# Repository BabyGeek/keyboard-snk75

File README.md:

# keyboard SnK<sup>75</sup>

V1 prototype in progress

----

The name "SnK<sup>75</sup>" come from my online name MrSnkiiKyz and 75 because it is a 75% layout

### Pictures will go there when V1 prototype will be done

## Features scheduled
* The PCB
    * handle up to 84 MX Swicthes
    * USB-C connected
    * RGB backligt for each swicth (South facing)
    * RGB Underglow
    * programmable with QMK
* The Layout is ISO only (Layout legends based on MacOS ISO-FR layout)
* 7° Typing angle case

## Features done
* The keyboard layout YES - you can [check it there](http://www.keyboard-layout-editor.com/##@@_a:7%3B&=Esc&=%0A%0A%0A%0AF1&=%0A%0A%0A%0AF2&=%0A%0A%0A%0AF3&=%0A%0A%0A%0AF4&=%0A%0A%0A%0AF5&=%0A%0A%0A%0AF6&=%0A%0A%0A%0AF7&=%0A%0A%0A%0AF8&=%0A%0A%0A%0AF9&=%0A%0A%0A%0AF10&=%0A%0A%0A%0AF11&=%0A%0A%0A%0AF12&=&=&=%3B&@_a:0%3B&=%23%0A%0A%0A%2F@%0A~%0A%60&=%0A%0A%0A%2F&%0A!%0A1&=%0A%0A%0Aé%0A%2F@%0A2&=%0A%0A%0A%22%0A%23%0A3&=%0A%0A%0A'%0A$%0A4&=%0A%0A%0A(%0A%25%0A5&=%0A%0A%0A§%0A%5E%0A6&=%0A%0A%0Aè%0A%2F&%0A7&=%0A%0A%0A!%0A*%0A8&=%0A%0A%0Aç%0A(%0A9&=%0A%0A%0Aà%0A)%0A0&=%25%0A%0A%0A)%0A%2F_%0A-&=%2F_%0A%0A%0A-%0A+%0A%2F=&_a:7&w:2%3B&=%0A%0A%0A%0ABackspace&=%0A%0A%0A%0AHome%3B&@_w:1.5%3B&=%0A%0A%0A%0ATab&_a:4%3B&=A%0A%0A%0A%0AQ&=Z%0A%0A%0A%0AW&=E%0A%0A%0A%0AE&=R%0A%0A%0A%0AR&=T%0A%0A%0A%0AT&=Y%0A%0A%0A%0AY&=U%0A%0A%0A%0AU&=I%0A%0A%0A%0AI&=O%0A%0A%0A%0AO&=P%0A%0A%0A%0AP&_a:0%3B&=¨%0A%0A%0A%5E%0A%7B%0A%5B&=*%0A%0A%0A€%0A%7D%0A%5D%0A%0A%0A%0A%0A$&_x:0.25&a:7&w:1.25&h:2&w2:1.5&h2:1&x2:-0.25%3B&=%0A%0A%0A%0AEnter&=%0A%0A%0A%0APage%20Up%3B&@_w:1.75%3B&=%0A%0A%0A%0ACaps%20Lock&_a:4%3B&=Q%0A%0A%0A%0AA&=S%0A%0A%0A%0AS&=D%0A%0A%0A%0AD&=F%0A%0A%0A%0AF&=G%0A%0A%0A%0AG&=H%0A%0A%0A%0AH&=J%0A%0A%0A%0AJ&=K%0A%0A%0A%0AK&=L%0A%0A%0A%0AL&_a:0%3B&=M%0A%0A%0A%0A%2F:%0A%2F%3B&=N%0A%0A%0A%0A%22%0A'&_a:4%3B&=£%0A%0A%0A%60&_x:1.25&a:7%3B&=%0A%0A%0A%0APage%20Down%3B&@_w:1.25%3B&=%0A%0A%0A%0AShift&_a:4%3B&=%3C%0A%0A%0A%3E&=W%0A%0A%0A%0AZ&=X%0A%0A%0A%0AX&=C%0A%0A%0A%0AC&=V%0A%0A%0A%0AV&=B%0A%0A%0A%0AB&=N%0A%0A%0A%0AN&=%3F%0A%0A%0A,%0AM&=.%0A,%0A%0A%2F%3B%0A%3C&=%2F%2F%0A.%0A%0A%2F:%0A%3E&_a:0%3B&=+%0A%0A%0A%2F=%0A%2F%2F%0A%3F&_a:7&w:1.75%3B&=%0A%0A%0A%0AShift&=%0A%0A%0A%0A↑&=%0A%0A%0A%0AEnd%3B&@_w:1.25%3B&=%0A%0A%0A%0ACtrl&_w:1.25%3B&=%0A%0A%0A%0AWin&_w:1.25%3B&=%0A%0A%0A%0AAlt&_w:6.25%3B&=&=%0A%0A%0A%0AAlt&=%0A%0A%0A%0AFn&=%0A%0A%0A%0ACtrl&=%0A%0A%0A%0A←&=%0A%0A%0A%0A↓&=%0A%0A%0A%0A→)

* The PCB schematics - YES it is supposed to be good
* The PCB Keys layout - YES
* The PCB Routes - In progress

### THEN 

* The PCB Prototype - Not yet
* Connectivity PCB Test - Not yet

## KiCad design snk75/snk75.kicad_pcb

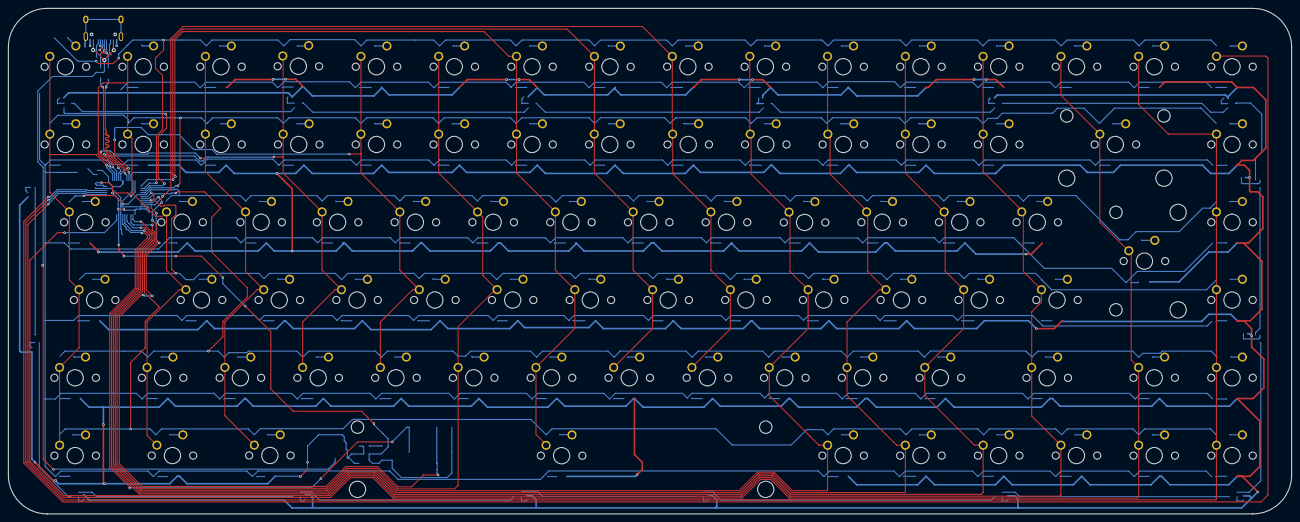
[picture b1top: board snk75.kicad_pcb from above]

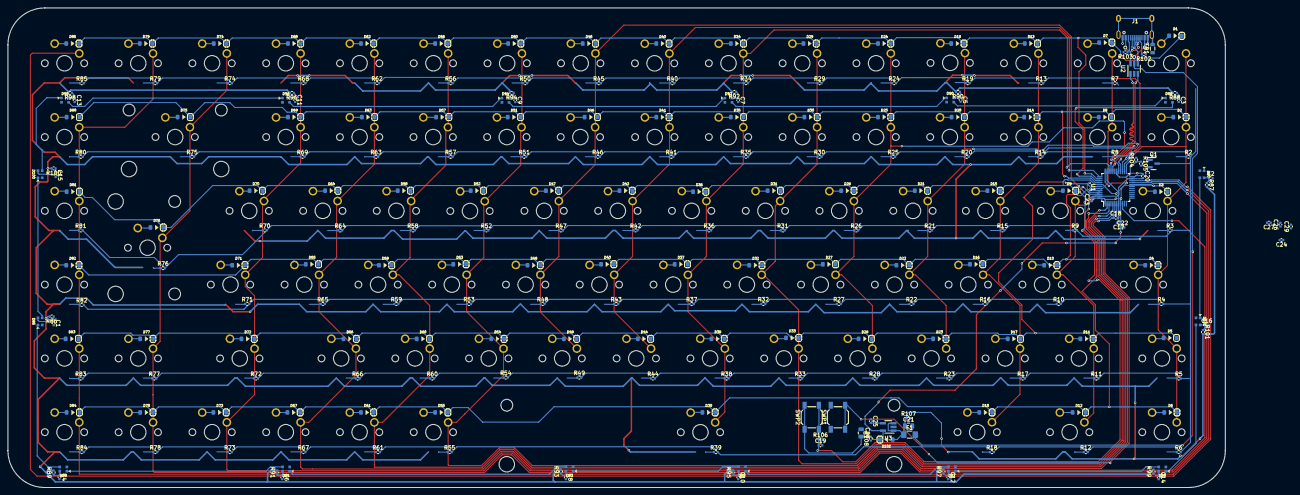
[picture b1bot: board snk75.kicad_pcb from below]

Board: 2 copper layers, 314.3 x 123.8 mm, 332 parts (247 on the bottom side), 156 nets.

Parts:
C1, C2, C3, C4, C5, C6, C7, C8, C9, C10, C11, C12, C13, C14, C15, C16, C17, C19, C23, C24, C26: 100nF; C_0402_1005Metric
C18: 100nF; C_0402_1005Metric_Pad0.74x0.62mm_HandSolder
C20: 1uF; C_0402_1005Metric
C21, C28: 1uF; C_0805_2012Metric
C22, C25: 10nF; C_0402_1005Metric
C27, C29: 4.7uF; C_0402_1005Metric
D1, D2, D3, D4, D5, D6, D7, D8, D9, D10, D11, D12, D13, D14, D15, D16, D17, D18, D19, D20, D21, D22, D23, D24, D25, D26, D27, D28, D29, D30, D31, D32, D33, D34, D35, D36, D37, D38, D39, D40, D41, D42, D43, D44, D45, D46, D47, D48, D49, D50, D51, D52, D53, D54, D55, D56, D57, D58, D59, D60, D61, D62, D63, D64, D65, D66, D67, D68, D69, D70, D71, D72, D73, D74, D75, D76, D77, D78, D79, D80, D81, D82, D83, D84, D85: 1N4148W; D_SOD-123
D86, D87, D88, D89, D90, D91, D92, D93, D94, D95, D96, D97, D98, D99, D100, D101: WS2812C-2020; LED_WS2812_2020
D102: B5819W-SL; D_SOD-123
F1: nSMD100-16V; Fuse_1206_3216Metric_Pad1.42x1.75mm_HandSolder
FB1: GZ2012D601TF; L_0805_2012Metric
J1: TYPE-C-31-M12; TYPE-C-31-M-12
MX1: Esc; MXOnly-1U-NoLED
MX2: @; MXOnly-1U-NoLED
MX3: Tab_15; MXOnly-1.5U-NoLED
MX4: Caps_175; MXOnly-1.75U-NoLED
MX5: LShift_125; MXOnly-1.25U-NoLED
MX6: Ctrl_125; MXOnly-1.25U-NoLED
MX7: F1; MXOnly-1U-NoLED
MX8: 1; MXOnly-1U-NoLED
MX9: A; MXOnly-1U-NoLED
MX10: Q; MXOnly-1U-NoLED
MX11: >; MXOnly-1U-NoLED
MX12: L_Opt_125; MXOnly-1.25U-NoLED
MX13: F2; MXOnly-1U-NoLED
MX14: 2; MXOnly-1U-NoLED
MX15: Z; MXOnly-1U-NoLED
MX16: S; MXOnly-1U-NoLED
MX17: W; MXOnly-1U-NoLED
MX18: L_Cmd_125; MXOnly-1.25U-NoLED
MX19: F3; MXOnly-1U-NoLED
MX20: 3; MXOnly-1U-NoLED
MX21: E; MXOnly-1U-NoLED
MX22: D; MXOnly-1U-NoLED
MX23: X; MXOnly-1U-NoLED
MX24: F4; MXOnly-1U-NoLED
MX25: 4; MXOnly-1U-NoLED
MX26: R; MXOnly-1U-NoLED
MX27: F; MXOnly-1U-NoLED
MX28: C; MXOnly-1U-NoLED
MX29: F5; MXOnly-1U-NoLED
MX30: 5; MXOnly-1U-NoLED
MX31: T; MXOnly-1U-NoLED
MX32: G; MXOnly-1U-NoLED
MX33: V; MXOnly-1U-NoLED
MX34: F6; MXOnly-1U-NoLED
MX35: 6; MXOnly-1U-NoLED
MX36: Y; MXOnly-1U-NoLED
MX37: H; MXOnly-1U-NoLED
MX38: B; MXOnly-1U-NoLED
MX39: Space_625; MXOnly-6.25U-NoLED
MX40: F7; MXOnly-1U-NoLED
MX41: 7; MXOnly-1U-NoLED
MX42: U; MXOnly-1U-NoLED
MX43: J; MXOnly-1U-NoLED
MX44: N; MXOnly-1U-NoLED
MX45: F8; MXOnly-1U-NoLED
MX46: 8; MXOnly-1U-NoLED
MX47: I; MXOnly-1U-NoLED
MX48: K; MXOnly-1U-NoLED
MX49: ?; MXOnly-1U-NoLED
MX50: F9; MXOnly-1U-NoLED
MX51: 9; MXOnly-1U-NoLED
MX52: O; MXOnly-1U-NoLED
MX53: L; MXOnly-1U-NoLED
MX54: .; MXOnly-1U-NoLED
MX55: R_Cmd; MXOnly-1U-NoLED
MX56: F10; MXOnly-1U-NoLED
MX57: 0; MXOnly-1U-NoLED
MX58: P; MXOnly-1U-NoLED
MX59: M; MXOnly-1U-NoLED
MX60: /; MXOnly-1U-NoLED
MX61: FN; MXOnly-1U-NoLED
MX62: F11; MXOnly-1U-NoLED
MX63: ); MXOnly-1U-NoLED
MX64: ¨; MXOnly-1U-NoLED
MX65: %; MXOnly-1U-NoLED
MX66: +; MXOnly-1U-NoLED
MX67: R_Opt; MXOnly-1U-NoLED
MX68: F12; MXOnly-1U-NoLED
MX69: -; MXOnly-1U-NoLED
MX70: *; MXOnly-1U-NoLED
MX71: £; MXOnly-1U-NoLED
MX72: RShift_175; MXOnly-1.75U-NoLED
MX73: A_L; MXOnly-1U-NoLED
MX74: F13; MXOnly-1U-NoLED
MX75: BckSpc_2; MXOnly-2U-NoLED
MX76: Enter_ISO_125_2; MXOnly-ISO-NoLED
MX77: A_UP; MXOnly-1U-NoLED
MX78: A_DWN; MXOnly-1U-NoLED
MX79: F14; MXOnly-1U-NoLED
MX80: Home; MXOnly-1U-NoLED
MX81: PgUp; MXOnly-1U-NoLED
MX82: PgDown; MXOnly-1U-NoLED
MX83: End; MXOnly-1U-NoLED
MX84: A_R; MXOnly-1U-NoLED
MX85: F15; MXOnly-1U-NoLED
Q1: AO3400A; SOT-23
R2, R3, R4, R5, R6, R7, R8, R9, R10, R11, R12, R13, R14, R15, R16, R17, R18, R19, R20, R21, R22, R23, R24, R25, R26, R27, R28, R29, R30, R31, R32, R33, R34, R35, R36, R37, R38, R39, R40, R41, R42, R43, R44, R45, R46, R47, R48, R49, R50, R51, R52, R53, R54, R55, R56, R57, R58, R59, R60, R61, R62, R63, R64, R65, R66, R67, R68, R69, R70, R71, R72, R73, R74, R75, R76, R77, R78, R79, R80, R81, R82, R83, R84, R85: 680R; R_0402_1005Metric
R86, R87, R88, R89, R90, R91, R92, R93, R94, R95, R96, R97, R98, R99, R100, R101: 5.1R; R_0402_1005Metric
R102, R103: 5.1k; R_0402_1005Metric
R104, R106: 10k; R_0402_1005Metric
R105: 100R; R_0402_1005Metric
R107, R108: 100k; R_0402_1005Metric
SWP1: SW_Push_RST; SW_SPST_SKQG_WithStem
SWP2: SW_Push_BOOT; SW_SPST_SKQG_WithStem
U1: STM32F072C8Tx; LQFP-48_7x7mm_P0.5mm
U2: USBLC6-2SC6; SOT-23-6_Handsoldering
U3: SGM2007-3.3XN5/TR; SOT-23-5_HandSoldering

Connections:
+3V3: C17.1, C20.1, C22.1, C23.1, C24.1, C26.1, C27.1, C28.2, C29.1, D102.1 (K), R108.2, SWP2.1, U1.1 (VBAT), U1.9 (VDDA), U1.24 (VDD), U1.36 (VDDIO2), U1.48 (VDD), U3.5 (OUT)
+5V: C21.1, D102.2 (A), F1.1, R86.2, R87.2, R88.2, R89.2, R90.2, R91.2, R92.2, R93.2, R94.2, R95.2, R96.2, R97.2, R98.2, R99.2, R100.2, R101.2, R107.1, U3.1 (IN), U3.3 (EN)
BOOT: C19.1, R106.1, SWP2.2, U1.44 (BOOT0)
D+: U1.33 (PA12), U2.1 (I/O1)
D-: U1.32 (PA11), U2.3 (I/O2)
DBUS+: J1.A6 (D+), J1.B6 (D+), U2.6 (I/O1)
DBUS-: J1.A7 (D-), J1.B7 (D-), U2.4 (I/O2)
GND: C1.2, C2.2, C3.2, C4.2, C5.2, C6.2, C7.2, C8.2, C9.2, C10.2, C11.2, C12.2, C13.2, C14.2, C15.2, C16.2, C17.2, C18.2, C19.2, C20.2, C21.2, C22.2, C23.2, C24.2, C25.1, C26.2, C27.2, C28.1, C29.2, D86.2 (VSS), D87.2 (VSS), D88.2 (VSS), D89.2 (VSS), D90.2 (VSS), D91.2 (VSS), D92.2 (VSS), D93.2 (VSS), D94.2 (VSS), D95.2 (VSS), D96.2 (VSS), D97.2 (VSS), D98.2 (VSS), D99.2 (VSS), D100.2 (VSS), D101.2 (VSS), FB1.1, J1.A1 (GND), J1.B1 (GND), Q1.2 (S), R102.1, R103.2, R104.2, R106.2, R107.2, R108.1, SWP1.1, U1.8 (VSSA), U1.23 (VSS), U1.35 (VSS), U1.47 (VSS), U2.2 (GND), U3.2 (GND)
GNDPWR: FB1.2, J1.S (SHIELD)
LED-: Q1.3 (D), R2.2, R3.2, R4.2, R5.2, R6.2, R7.2, R8.2, R9.2, R10.2, R11.2, R12.2, R13.2, R14.2, R15.2, R16.2, R17.2, R18.2, R19.2, R20.2, R21.2, R22.2, R23.2, R24.2, R25.2, R26.2, R27.2, R28.2, R29.2, R30.2, R31.2, R32.2, R33.2, R34.2, R35.2, R36.2, R37.2, R38.2, R39.2, R40.2, R41.2, R42.2, R43.2, R44.2, R45.2, R46.2, R47.2, R48.2, R49.2, R50.2, R51.2, R52.2, R53.2, R54.2, R55.2, R56.2, R57.2, R58.2, R59.2, R60.2, R61.2, R62.2, R63.2, R64.2, R65.2, R66.2, R67.2, R68.2, R69.2, R70.2, R71.2, R72.2, R73.2, R74.2, R75.2, R76.2, R77.2, R78.2, R79.2, R80.2, R81.2, R82.2, R83.2, R84.2, R85.2
LED_PWM: R104.1, R105.1, U1.30 (PA9)
unnamed: C1.1, D86.4 (VDD), R86.1
unnamed: C2.1, D87.4 (VDD), R87.1
unnamed: C3.1, D88.4 (VDD), R88.1
unnamed: C4.1, D89.4 (VDD), R89.1
unnamed: C5.1, D90.4 (VDD), R90.1
unnamed: C6.1, D91.4 (VDD), R91.1
unnamed: C7.1, D92.4 (VDD), R92.1
unnamed: C8.1, D93.4 (VDD), R93.1
unnamed: C9.1, D94.4 (VDD), R94.1
unnamed: C10.1, D95.4 (VDD), R95.1
unnamed: C11.1, D96.4 (VDD), R96.1
unnamed: C12.1, D97.4 (VDD), R97.1
unnamed: C13.1, D98.4 (VDD), R98.1
unnamed: C14.1, D99.4 (VDD), R99.1
unnamed: C15.1, D100.4 (VDD), R100.1
unnamed: C16.1, D101.4 (VDD), R101.1
unnamed: C25.2, U3.4 (BP/FB)
unnamed: D1.2 (A), MX1.2 (ROW)
unnamed: D2.2 (A), MX2.2 (ROW)
unnamed: D3.2 (A), MX3.2 (ROW)
unnamed: D4.2 (A), MX4.2 (ROW)
unnamed: D5.2 (A), MX5.2 (ROW)
unnamed: D6.2 (A), MX6.2 (ROW)
unnamed: D7.2 (A), MX7.2 (ROW)
unnamed: D8.2 (A), MX8.2 (ROW)
unnamed: D9.2 (A), MX9.2 (ROW)
unnamed: D10.2 (A), MX10.2 (ROW)
unnamed: D11.2 (A), MX11.2 (ROW)
unnamed: D12.2 (A), MX12.2 (ROW)
unnamed: D13.2 (A), MX13.2 (ROW)
unnamed: D14.2 (A), MX14.2 (ROW)
unnamed: D15.2 (A), MX15.2 (ROW)
unnamed: D16.2 (A), MX16.2 (ROW)
unnamed: D17.2 (A), MX17.2 (ROW)
unnamed: D18.2 (A), MX18.2 (ROW)
unnamed: D19.2 (A), MX19.2 (ROW)
unnamed: D20.2 (A), MX20.2 (ROW)
unnamed: D21.2 (A), MX21.2 (ROW)
unnamed: D22.2 (A), MX22.2 (ROW)
unnamed: D23.2 (A), MX23.2 (ROW)
unnamed: D24.2 (A), MX24.2 (ROW)
unnamed: D25.2 (A), MX25.2 (ROW)
unnamed: D26.2 (A), MX26.2 (ROW)
unnamed: D27.2 (A), MX27.2 (ROW)
unnamed: D28.2 (A), MX28.2 (ROW)
unnamed: D29.2 (A), MX29.2 (ROW)
unnamed: D30.2 (A), MX30.2 (ROW)
unnamed: D31.2 (A), MX31.2 (ROW)
unnamed: D32.2 (A), MX32.2 (ROW)
unnamed: D33.2 (A), MX33.2 (ROW)
unnamed: D34.2 (A), MX34.2 (ROW)
unnamed: D35.2 (A), MX35.2 (ROW)
unnamed: D36.2 (A), MX36.2 (ROW)
unnamed: D37.2 (A), MX37.2 (ROW)
unnamed: D38.2 (A), MX38.2 (ROW)
unnamed: D39.2 (A), MX39.2 (ROW)
unnamed: D40.2 (A), MX40.2 (ROW)
unnamed: D41.2 (A), MX41.2 (ROW)
unnamed: D42.2 (A), MX42.2 (ROW)
unnamed: D43.2 (A), MX43.2 (ROW)
unnamed: D44.2 (A), MX44.2 (ROW)
unnamed: D45.2 (A), MX45.2 (ROW)
unnamed: D46.2 (A), MX46.2 (ROW)
unnamed: D47.2 (A), MX47.2 (ROW)
unnamed: D48.2 (A), MX48.2 (ROW)
unnamed: D49.2 (A), MX49.2 (ROW)
unnamed: D50.2 (A), MX50.2 (ROW)
unnamed: D51.2 (A), MX51.2 (ROW)
unnamed: D52.2 (A), MX52.2 (ROW)
unnamed: D53.2 (A), MX53.2 (ROW)
unnamed: D54.2 (A), MX54.2 (ROW)
unnamed: D55.2 (A), MX55.2 (ROW)
unnamed: D56.2 (A), MX56.2 (ROW)
unnamed: D57.2 (A), MX57.2 (ROW)
unnamed: D58.2 (A), MX58.2 (ROW)
unnamed: D59.2 (A), MX59.2 (ROW)
unnamed: D60.2 (A), MX60.2 (ROW)
unnamed: D61.2 (A), MX61.2 (ROW)
unnamed: D62.2 (A), MX62.2 (ROW)
unnamed: D63.2 (A), MX63.2 (ROW)
unnamed: D64.2 (A), MX64.2 (ROW)
unnamed: D65.2 (A), MX65.2 (ROW)
unnamed: D66.2 (A), MX66.2 (ROW)
unnamed: D67.2 (A), MX67.2 (ROW)
unnamed: D68.2 (A), MX68.2 (ROW)
unnamed: D69.2 (A), MX69.2 (ROW)
unnamed: D70.2 (A), MX70.2 (ROW)
unnamed: D71.2 (A), MX71.2 (ROW)
unnamed: D72.2 (A), MX72.2 (ROW)
unnamed: D73.2 (A), MX73.2 (ROW)
unnamed: D74.2 (A), MX74.2 (ROW)
unnamed: D75.2 (A), MX75.2 (ROW)
unnamed: D76.2 (A), MX76.2 (ROW)
unnamed: D77.2 (A), MX77.2 (ROW)
unnamed: D78.2 (A), MX78.2 (ROW)
unnamed: D79.2 (A), MX79.2 (ROW)
unnamed: D80.2 (A), MX80.2 (ROW)
unnamed: D81.2 (A), MX81.2 (ROW)
unnamed: D82.2 (A), MX82.2 (ROW)
unnamed: D83.2 (A), MX83.2 (ROW)
unnamed: D84.2 (A), MX84.2 (ROW)
unnamed: D85.2 (A), MX85.2 (ROW)
unnamed: D86.1 (DOUT), D89.3 (DIN)
unnamed: D88.1 (DOUT), D90.3 (DIN)
unnamed: D89.1 (DOUT), D91.3 (DIN)
unnamed: D90.1 (DOUT), D92.3 (DIN)
unnamed: D91.1 (DOUT), D93.3 (DIN)
unnamed: D92.1 (DOUT), D94.3 (DIN)
unnamed: D93.1 (DOUT), D95.3 (DIN)
unnamed: D94.1 (DOUT), D96.3 (DIN)
unnamed: D95.1 (DOUT), D97.3 (DIN)
unnamed: D96.1 (DOUT), D98.3 (DIN)
unnamed: D97.1 (DOUT), D99.3 (DIN)
unnamed: D86.3 (DIN), D100.1 (DOUT)
unnamed: D98.1 (DOUT), D100.3 (DIN)
unnamed: D87.3 (DIN), D101.1 (DOUT)
unnamed: D99.1 (DOUT), D101.3 (DIN)
unnamed: J1.A5 (CC1), R102.2
unnamed: J1.B5 (CC2), R103.1
unnamed: Q1.1 (G), R105.2
RST: C18.1, SWP1.2, U1.7 (NRST)
UGLED: D88.3 (DIN), U1.39 (PB3)
VBUS: F1.2, J1.A4 (VBUS), J1.B4 (VBUS), U2.5 (VBUS)
col1: MX1.1 (COL), MX2.1 (COL), MX3.1 (COL), MX4.1 (COL), MX5.1 (COL), MX6.1 (COL), U1.25 (PB12)
col2: MX7.1 (COL), MX8.1 (COL), MX9.1 (COL), MX10.1 (COL), MX11.1 (COL), MX12.1 (COL), U1.26 (PB13)
col3: MX13.1 (COL), MX14.1 (COL), MX15.1 (COL), MX16.1 (COL), MX17.1 (COL), MX18.1 (COL), U1.27 (PB14)
col4: MX19.1 (COL), MX20.1 (COL), MX21.1 (COL), MX22.1 (COL), MX23.1 (COL), U1.28 (PB15)
col5: MX24.1 (COL), MX25.1 (COL), MX26.1 (COL), MX27.1 (COL), MX28.1 (COL), U1.29 (PA8)
col6: MX29.1 (COL), MX30.1 (COL), MX31.1 (COL), MX32.1 (COL), MX33.1 (COL), U1.3 (PC14)
col7: MX34.1 (COL), MX35.1 (COL), MX36.1 (COL), MX37.1 (COL), MX38.1 (COL), MX39.1 (COL), U1.34 (PA13)
col8: MX40.1 (COL), MX41.1 (COL), MX42.1 (COL), MX43.1 (COL), MX44.1 (COL), U1.37 (PA14)
col9: MX45.1 (COL), MX46.1 (COL), MX47.1 (COL), MX48.1 (COL), MX49.1 (COL), U1.46 (PB9)
col10: MX50.1 (COL), MX51.1 (COL), MX52.1 (COL), MX53.1 (COL), MX54.1 (COL), MX55.1 (COL), U1.2 (PC13)
col11: MX56.1 (COL), MX57.1 (COL), MX58.1 (COL), MX59.1 (COL), MX60.1 (COL), MX61.1 (COL), U1.5 (PF0)
col12: MX62.1 (COL), MX63.1 (COL), MX64.1 (COL), MX65.1 (COL), MX66.1 (COL), MX67.1 (COL), U1.6 (PF1)
col13: MX68.1 (COL), MX69.1 (COL), MX70.1 (COL), MX71.1 (COL), MX72.1 (COL), MX73.1 (COL), U1.10 (PA0)
col14: MX74.1 (COL), MX75.1 (COL), MX76.1 (COL), MX77.1 (COL), MX78.1 (COL), U1.20 (PB2)
col15: MX79.1 (COL), MX80.1 (COL), MX81.1 (COL), MX82.1 (COL), MX83.1 (COL), MX84.1 (COL), U1.21 (PB10)
col16: MX85.1 (COL), U1.22 (PB11)
row1: D1.1 (K), D7.1 (K), D13.1 (K), D19.1 (K), D24.1 (K), D29.1 (K), D34.1 (K), D40.1 (K), D45.1 (K), D50.1 (K), D56.1 (K), D62.1 (K), D68.1 (K), D74.1 (K), D79.1 (K), D85.1 (K), U1.38 (PA15)
row2: D2.1 (K), D8.1 (K), D14.1 (K), D20.1 (K), D25.1 (K), D30.1 (K), D35.1 (K), D41.1 (K), D46.1 (K), D51.1 (K), D57.1 (K), D63.1 (K), D69.1 (K), D75.1 (K), D80.1 (K), U1.40 (PB4)
row3: D3.1 (K), D9.1 (K), D15.1 (K), D21.1 (K), D26.1 (K), D31.1 (K), D36.1 (K), D42.1 (K), D47.1 (K), D52.1 (K), D58.1 (K), D64.1 (K), D70.1 (K), D76.1 (K), D81.1 (K), U1.41 (PB5)
row4: D4.1 (K), D10.1 (K), D16.1 (K), D22.1 (K), D27.1 (K), D32.1 (K), D37.1 (K), D43.1 (K), D48.1 (K), D53.1 (K), D59.1 (K), D65.1 (K), D71.1 (K), D82.1 (K), U1.42 (PB6)
row5: D5.1 (K), D11.1 (K), D17.1 (K), D23.1 (K), D28.1 (K), D33.1 (K), D38.1 (K), D44.1 (K), D49.1 (K), D54.1 (K), D60.1 (K), D66.1 (K), D72.1 (K), D77.1 (K), D83.1 (K), U1.43 (PB7)
row6: D6.1 (K), D12.1 (K), D18.1 (K), D39.1 (K), D55.1 (K), D61.1 (K), D67.1 (K), D73.1 (K), D78.1 (K), D84.1 (K), U1.45 (PB8)

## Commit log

2022-05-26 Add submodules library
2022-05-26 Added PCB started project
2022-05-26 Add ubc c connector
2022-05-26 Add submodule Archeon symbols
2022-05-26 Add gitignore
2022-05-26 Start keys layout
2022-05-26 Update gitignore
2022-05-26 feat: keyboard keys
2022-05-27 Added submodules footprints, and devided main pcb into pin sheets
2022-05-27 backup zip
2022-05-27 Add keys row 2
2022-05-27 Added other keys
2022-05-27 Added u for not 1 unit keys
2022-05-27 Added u for not space
2022-05-27 Added footprints for units more than 1
2022-05-27 Began PCB design
2022-05-27 Switch layout on PCB Editor
2022-05-27 Added PCB rounded borders
2022-05-27 Fixed reset
2022-05-27 Fixed label
2022-05-28 Began routing
2022-05-29 Changed MCU for STM32F072C8Tx and wired cols and rows
2022-05-30 added new row layout and connected row1 to MCU
2022-05-30 fixed alignment for unused pins
2022-05-30 added components on board and began routing
2022-05-31 Added some routes and finished to align components on switches
2022-05-31 routed all rows and backlight RGB
2022-05-31 Routed rows to MCU and began cols
2022-06-01 WIP: Removed wrong path, gonna rebuild with better designed path
2022-06-01 Re routed paths for cols and rows
2022-06-01 added forgotten col10
2022-06-06 WIP routes
2022-06-06 WIP(3D models): added library with models
2022-06-06 WIP(3D models): added R1 models
2022-06-15 Nearly make all paths
2022-06-23 WIP: replacing backlight LEDs with RGB LEDs
2022-06-23 WIP: made all old LEDs no-connecting flags
